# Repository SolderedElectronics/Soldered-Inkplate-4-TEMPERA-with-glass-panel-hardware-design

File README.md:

## Soldered Inkplate 4 TEMPERA with glass panel hardware design

|  |
| :----------------------------------------------------------: |
|      [Soldered Inkplate 4 TEMPERA with glass panel](https://soldered.com/product/soldered-inkplate-4-tempera/)      |

Inkplate 4 TEMPERA is an easy-to-use, all-in-one device that puts the power of e-paper technology in the palm of your hand. Behind its 3.8-inch, 600×600-pixel e-paper touchscreen, it packs the following features into one compact, elegant package: frontlighting, an abundance of sensors, Wi-Fi and Bluetooth connectivity, a built-in battery, and a low-power operating mode.

## Repository contents

All Soldered hardware is designed in KiCAD, and repositories are organized in the following way:

- CAD folder - contains KiCAD files (Schematics, Board, Panel Board), organized by version. Change log lists all changes between versions.
- OUTPUTS - contains useful files, such as Bill of Materials (BOM), PDF of schematics, 3D .step file of the board and gerber files, organized by version. 

## Want to contribute?

All contributions are welcome, feel free to submit the pull request. If you discover a bug, please submit an issue or pull request. 

## About Soldered

At Soldered, we design and manufacture a wide selection of electronic products to help you turn your ideas into acts and bring you one step closer to your final project. Our products are intented for makers and crafted in-house by our experienced team in Osijek, Croatia. We believe that sharing is a crucial element for improvement and innovation, and we work hard to stay connected with all our makers regardless of their skill or experience level. Therefore, all our products are open-source. Finally, we always have your back. If you face any problem concerning either your shopping experience or your electronics project, our team will help you deal with it, offering efficient customer service and cost-free technical support anytime. Some of those might be useful for you:

- [Web Store](https://www.soldered.com)
- [Tutorials & Projects](https://learn.soldered.com)
- [Community & Technical support](https://community.soldered.com)
- [Custom PCBs](https://pcb.soldered.com)

## License info

All Soldered open-source hardware (OSH) is under The TAPR Open Hardware License. Read more in the LICENSE file. 

No warranty - all designs in this repository are distributed in the hope that they will be useful, but without any warranty. They are provided "AS IS", therefore without warranty of any kind, either expressed or implied. The entire quality and performance of what you do with the contents of this repository are your responsibility. In no event, Soldered (TAVU) will be liable for your damages, losses, including any general, special, incidental or consequential damage arising out of the use or inability to use the contents of this repository. 

Thank you from your fellow makers at Soldered.

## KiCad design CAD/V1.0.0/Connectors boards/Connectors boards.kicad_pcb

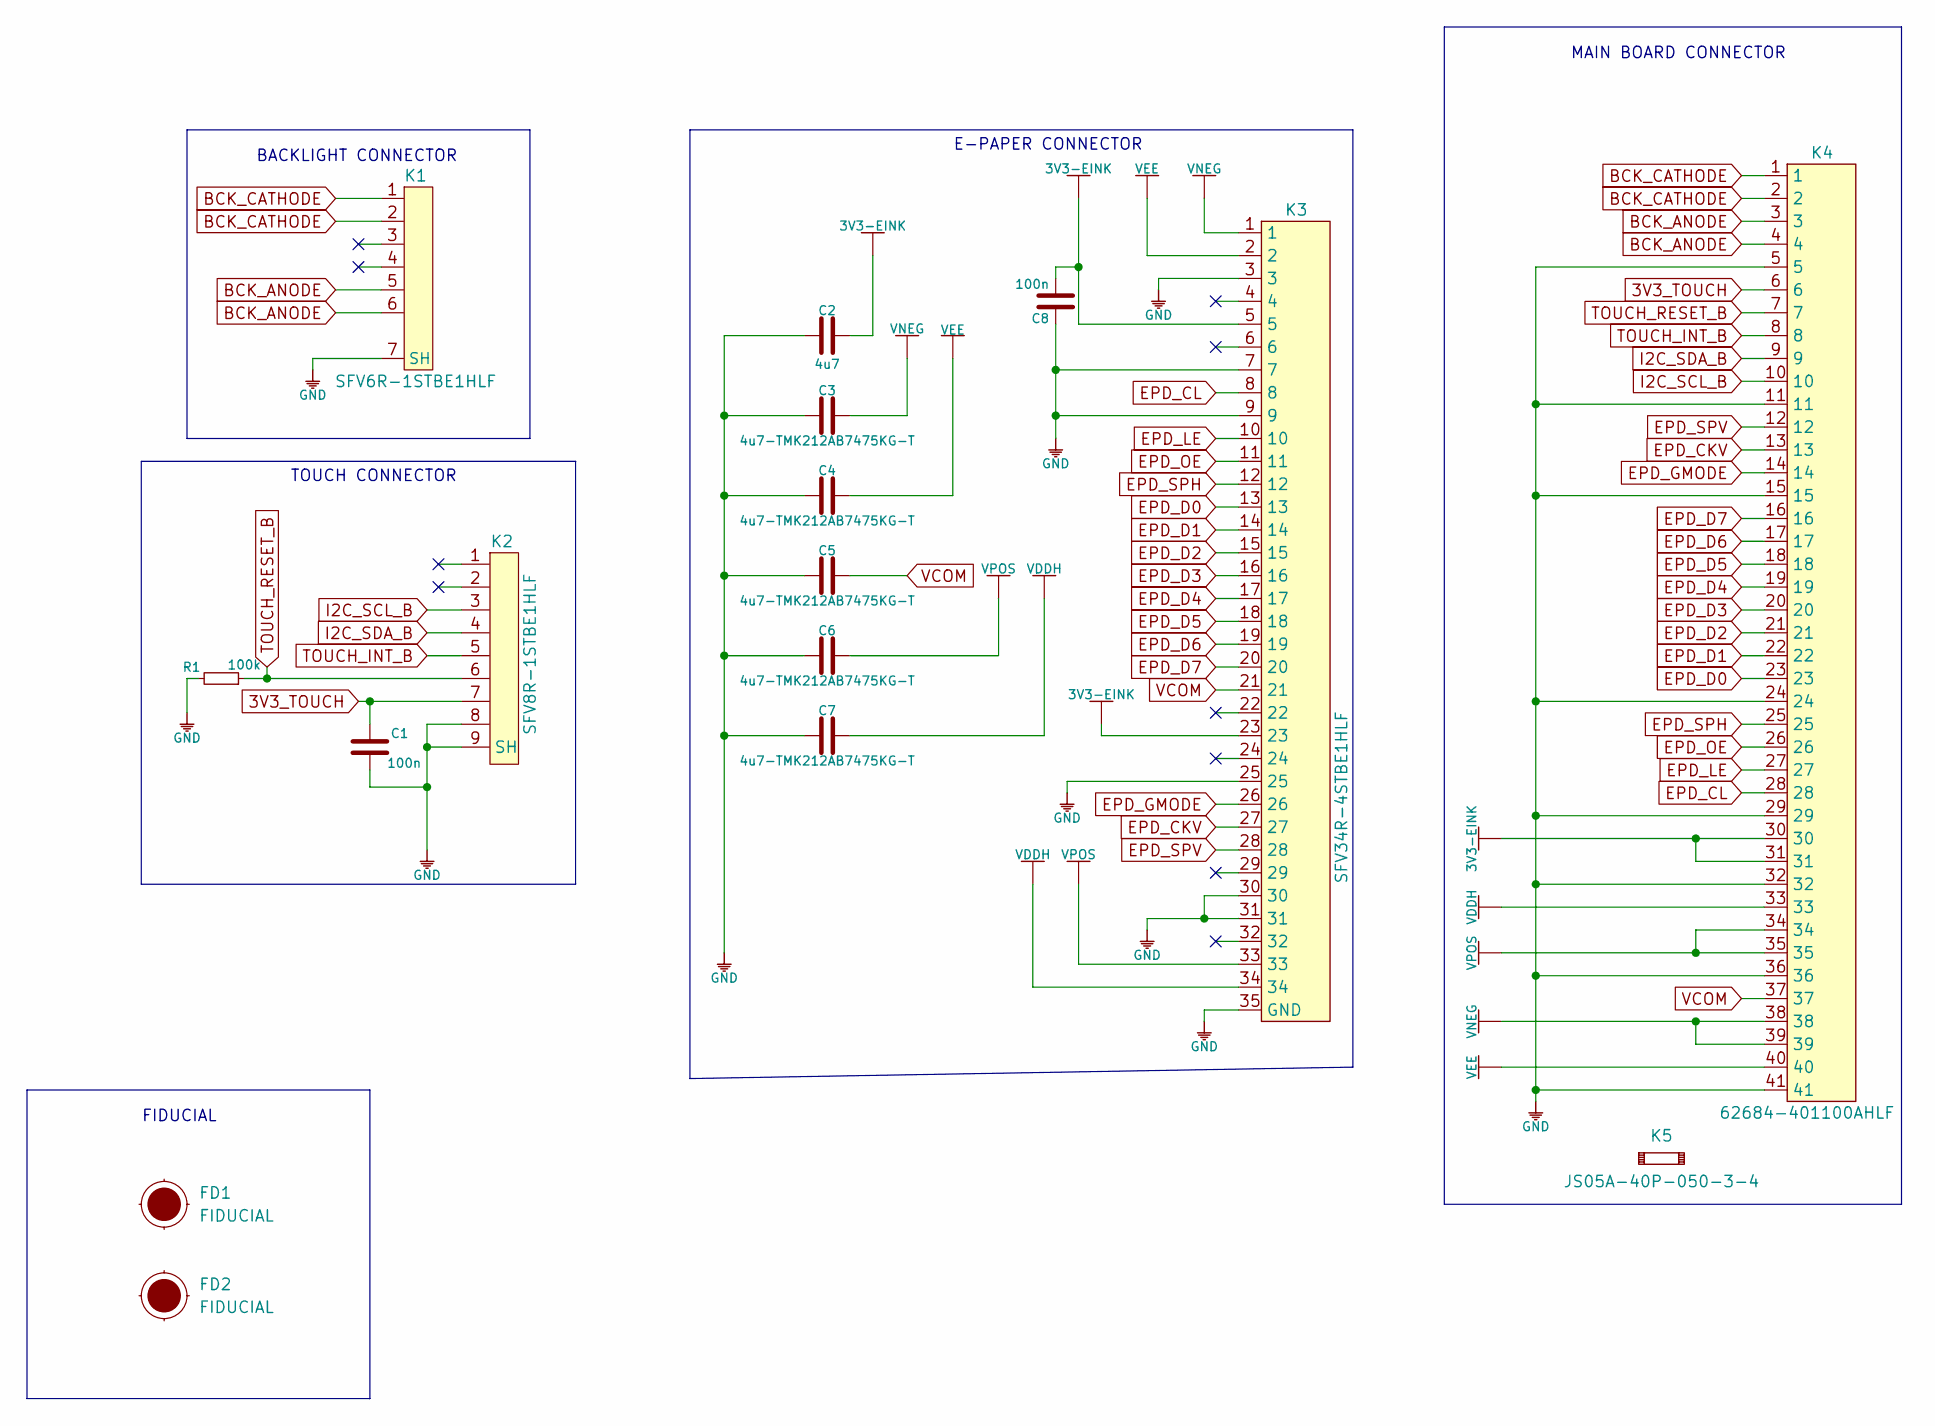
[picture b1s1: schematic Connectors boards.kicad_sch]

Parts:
C1, C8: 100n; 0603C
C2: 4u7; 0603C
C3, C4, C5, C6, C7: 4u7-TMK212AB7475KG-T; 0805C
FD1, FD2: FIDUCIAL; FIDUCIAL_23
K1: SFV6R-1STBE1HLF
K2: SFV8R-1STBE1HLF
K3: SFV34R-4STBE1HLF
K4: 62684-401100AHLF
K5: JS05A-40P-050-3-4
R1: 100k; 0603R

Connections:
3V3-EINK: C2.2, C8.1, K3.5, K3.23, K4.30, K4.31
3V3_TOUCH: C1.2, K2.7, K4.6
BCK_ANODE: K1.5, K1.6, K4.3, K4.4
BCK_CATHODE: K1.1, K1.2, K4.1, K4.2
EPD_CKV: K3.27, K4.13
EPD_CL: K3.8, K4.28
EPD_D0: K3.13, K4.23
EPD_D1: K3.14, K4.22
EPD_D2: K3.15, K4.21
EPD_D3: K3.16, K4.20
EPD_D4: K3.17, K4.19
EPD_D5: K3.18, K4.18
EPD_D6: K3.19, K4.17
EPD_D7: K3.20, K4.16
EPD_GMODE: K3.26, K4.14
EPD_LE: K3.10, K4.27
EPD_OE: K3.11, K4.26
EPD_SPH: K3.12, K4.25
EPD_SPV: K3.28, K4.12
GND: C1.1, C2.1, C3.1, C4.1, C5.1, C6.1, C7.1, C8.2, K1.7 (SH), K2.8, K2.9 (SH), K3.3, K3.7, K3.9, K3.25, K3.30, K3.31, K3.35 (GND), K4.5, K4.11, K4.15, K4.24, K4.29, K4.32, K4.36, K4.41, R1.2
I2C_SCL_B: K2.3, K4.10
I2C_SDA_B: K2.4, K4.9
TOUCH_INT_B: K2.5, K4.8
TOUCH_RESET_B: K2.6, K4.7, R1.1
VCOM: C5.2, K3.21, K4.37
VDDH: C7.2, K3.34, K4.33
VEE: C4.2, K3.2, K4.40
VNEG: C3.2, K3.1, K4.38, K4.39
VPOS: C6.2, K3.33, K4.34, K4.35

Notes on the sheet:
TOUCH CONNECTOR
FIDUCIAL
E-PAPER CONNECTOR
BACKLIGHT CONNECTOR
MAIN BOARD CONNECTOR

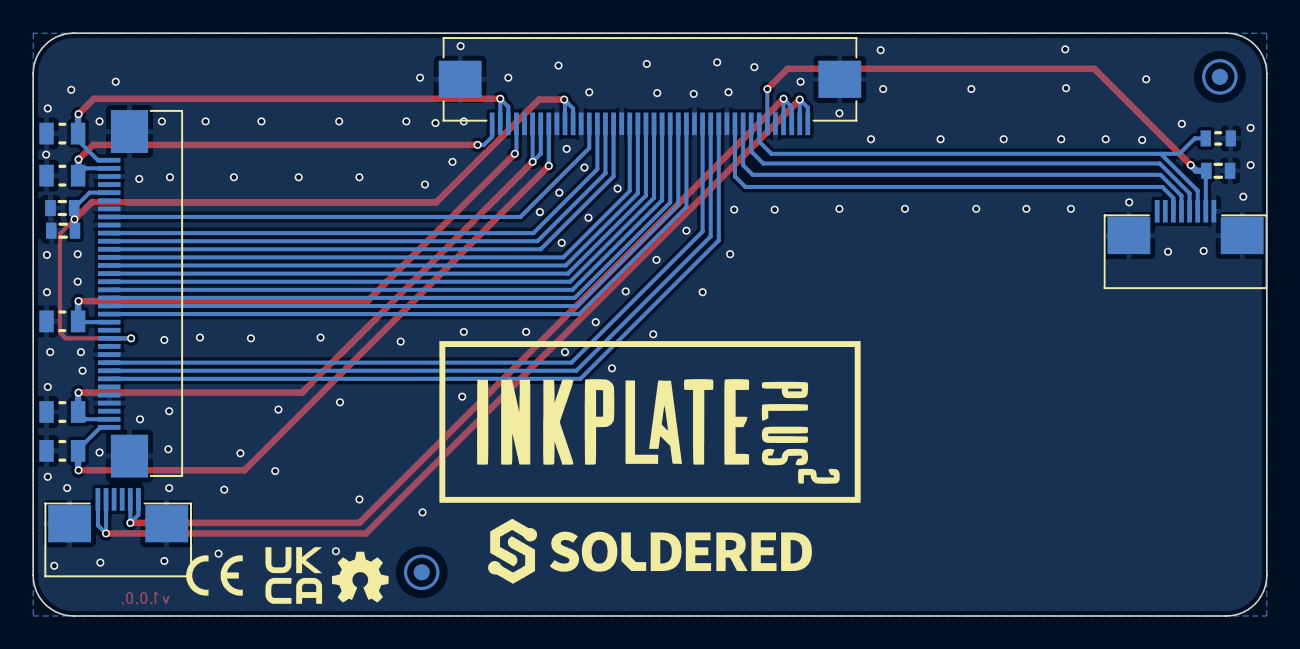
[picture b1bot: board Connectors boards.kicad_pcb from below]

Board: 2 copper layers, 76.2 x 36.0 mm, 17 parts (15 on the bottom side), 29 nets.

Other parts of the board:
Ref**: Val**; Version1.0.0.

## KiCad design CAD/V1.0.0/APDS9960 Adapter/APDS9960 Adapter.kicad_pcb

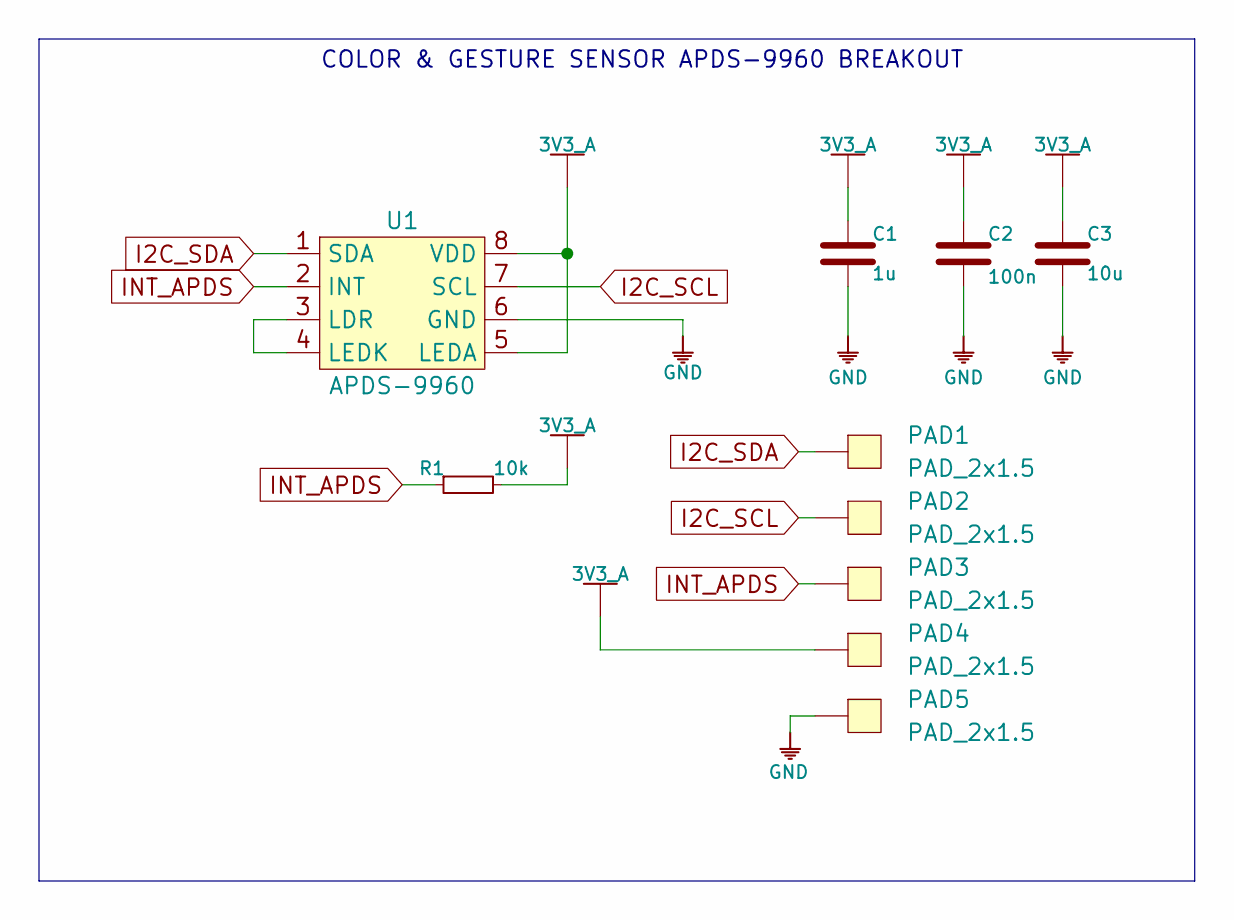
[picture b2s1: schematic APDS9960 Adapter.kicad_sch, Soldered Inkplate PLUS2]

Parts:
C1: 1u; 0603C
C2: 100n; 0603C
C3: 10u; 1206C
PAD1, PAD2, PAD3, PAD4, PAD5: PAD_2x1.5
R1: 10k; 0603R
U1: APDS-9960

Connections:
3V3_A: C1.2, C2.2, C3.2, PAD4.1, R1.2, U1.5 (LEDA), U1.8 (VDD)
GND: C1.1, C2.1, C3.1, PAD5.1, U1.6 (GND)
I2C_SCL: PAD2.1, U1.7 (SCL)
I2C_SDA: PAD1.1, U1.1 (SDA)
INT_APDS: PAD3.1, R1.1, U1.2 (INT)
unnamed: U1.3 (LDR), U1.4 (LEDK)

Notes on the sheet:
COLOR & GESTURE SENSOR APDS-9960 BREAKOUT

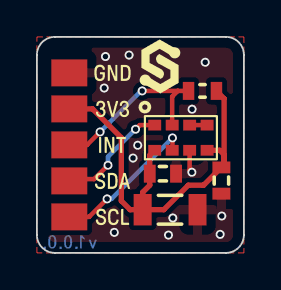
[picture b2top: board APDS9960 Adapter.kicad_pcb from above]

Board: 2 copper layers, 11.5 x 12.0 mm, 16 parts (1 on the bottom side), 6 nets.

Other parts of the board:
Ref**: Val**; Version1.0.0.
kibuzzard-6322F4B4: G***; kibuzzard-6322F4B4
kibuzzard-6322F4CC: G***; kibuzzard-6322F4CC
kibuzzard-6322F44C: G***; kibuzzard-6322F44C
kibuzzard-6322F444: G***; kibuzzard-6322F444
kibuzzard-6322F457: G***; kibuzzard-6322F457

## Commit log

2024-04-19 Init
